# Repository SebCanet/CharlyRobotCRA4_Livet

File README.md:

# CharlyRobotCRA4_Livet
GRBL Firmware:
- cpu_map.h probe pin (originally A5) sawped with soft reset pin (originally A0)

GRBL Configuration:
- limit switch backup distance changed from 1 to 2mm

ToDo List:
- Door switch firmware configuration and wiring
- 3D printed probe connector holder
- checking the grounding
- adding a 1M ohms resistor to the probe pin ?
- With a relay, cutting power to the arduino when the emergy stop switch is triggered

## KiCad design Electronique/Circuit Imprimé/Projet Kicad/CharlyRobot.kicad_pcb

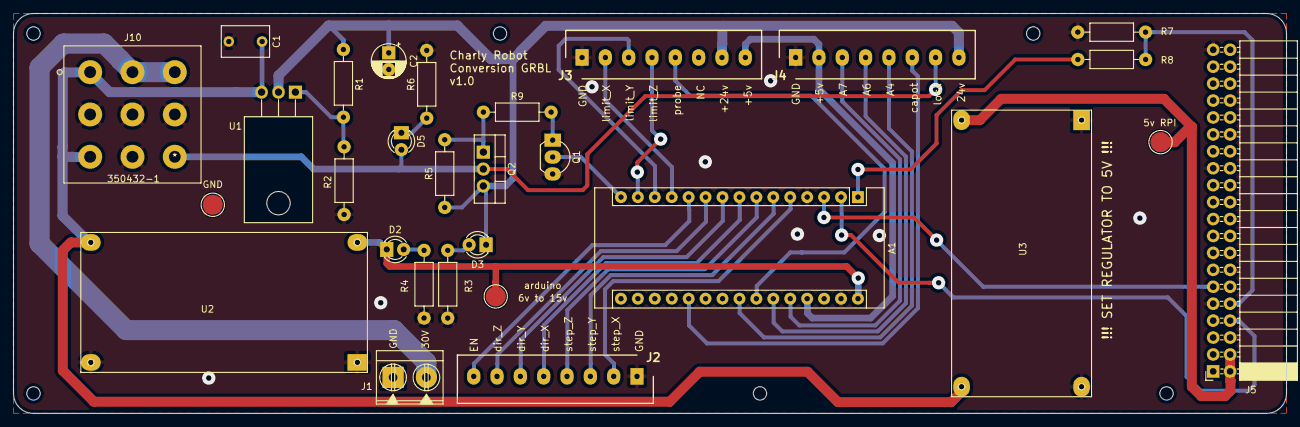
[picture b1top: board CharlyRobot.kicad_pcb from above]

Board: 2 copper layers, 191.0 x 60.0 mm, 29 parts (0 on the bottom side), 34 nets.

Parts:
5v RPI: TestPoint; TestPoint_Pad_D3.0mm
A1: Arduino_Nano_v2.x; Arduino_Nano
C1: 1µF; C_Rect_L7.0mm_W4.5mm_P5.00mm
C2: 10µF; CP_Radial_D5.0mm_P2.50mm
D2, D3, D5: LED; LED_D3.0mm
GND: TestPoint; TestPoint_Pad_D3.0mm
J1: Connector_Conn_01x02_Male; Bornier_2pts_L10mm_W8mm_P5mm
J2, J3, J4: Connector_Conn_01x08_Male; Bornier_8pins
J5: Connector_Raspberry_Pi_2_3; PinSocket_2x20_P2.54mm_Horizontal
J10: 350432-1
Q1: BS170; TO-92_Inline_Wide_large
Q2: IRF9540N; TO-220-3_INVERSE
R1, R4: 330; R_Axial_DIN0207_L6.3mm_D2.5mm_P10.16mm_Horizontal
R2: 2.7k; R_Axial_DIN0207_L6.3mm_D2.5mm_P10.16mm_Horizontal
R3, R7, R9: 1k; R_Axial_DIN0207_L6.3mm_D2.5mm_P10.16mm_Horizontal
R5: 10k; R_Axial_DIN0207_L6.3mm_D2.5mm_P10.16mm_Horizontal
R6, R8: 2.2k; R_Axial_DIN0207_L6.3mm_D2.5mm_P10.16mm_Horizontal
U1: LM317_TO3; TO-220-3_Horizontal_TabDown
U2, U3: regulateur_buck
arduino: TestPoint; TestPoint_Pad_D3.0mm

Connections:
+5V: A1.27, J3.8, J4.2
/A1: A1.20, J4.6
/A4: A1.23, J4.5
/A6: A1.25, J4.4
/A7: A1.26, J4.3
/RESET: A1.3, J5.11
/RX: A1.2, J5.8
/TX: A1.1, R7.1
/alim_arduino: A1.30, D2.1, U2.4, arduino.1
/alim_drivers: J1.2, J10.4, J10.7
/alim_relai: C2.1, D3.1, J3.7, J4.8, Q2.2, R1.1, R5.1, U1.3
/alim_rpi: 5v RPI.1, J5.2, J5.4, U3.4
/comm_electro: D5.2, J4.7, J10.9, Q2.3
/dir_X: A1.8, J2.5
/dir_Y: A1.9, J2.6
/dir_Z: A1.10, J2.7
/enable: A1.11, J2.8
/fraise: A1.15, Q1.2
/limit_X: A1.12, J3.2
/limit_Y: A1.13, J3.3
/limit_Z: A1.14, J3.4
/probe: A1.24, J3.5
/step_X: A1.5, J2.2
/step_Y: A1.6, J2.3
/step_Z: A1.7, J2.4
GND: A1.4, A1.29, C1.2, C2.2, GND.1, J1.1, J2.1, J3.1, J4.1, J5.6, J5.9, J5.14, J5.20, J5.25, J5.30, J5.34, J5.39, J10.2, J10.5, J10.6, J10.8, Q1.3, R2.2, R3.1, R4.1, R6.2, R8.2, U2.2, U2.3, U3.2, U3.3
unnamed: D2.2, R4.2
unnamed: D3.2, R3.2
unnamed: D5.1, R6.1
unnamed: J5.10, R7.2, R8.1
unnamed: Q1.1, R9.2
unnamed: Q2.1, R5.2, R9.1
unnamed: R1.2, R2.1, U1.1
VDD: C1.1, J10.1, J10.3, U1.2, U2.1, U3.1

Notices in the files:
parts and their libraries:
Copyright 2016 Accelerated Designs. All rights reserved.
